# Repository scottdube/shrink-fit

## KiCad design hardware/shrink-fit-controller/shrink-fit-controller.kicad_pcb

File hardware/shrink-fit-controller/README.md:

# Shrink-Fit Induction Controller — PCB

KiCad 10 project. **Milled in-house, single-sided**, so the constraints that
decide this layout are not the ones a board house would impose.

## Scope: full controller, staged populate

Decided 2026-08-25. Every Phase 2 block gets a footprint and a header; only the
Phase 1 blocks get populated now.

The reasoning is *not* the enclosure's "expensive to redo" argument — a milled
board is an afternoon, and copper is the cheap part. It is that **a respin costs
desoldering and re-soldering everything already on the board.** A footprint on a
board you are milling anyway costs nothing, so the asymmetry runs entirely one
way.

Rejected: a Phase-1-minimum board. It would route faster and mill sooner, but it
buys a few hours against a guaranteed rebuild of the one thing on this project
that has to be *reliable* rather than fast.

## Blocks

| | Block | Phase | Parts |
|---|---|---|---|
| ✅ | MCU | 1 | U1 ESP32-S3 Super Mini (HW-747) |
| ✅ | SSR drive | 1 | Q1 2N3904, R1 1 k |
| ✅ | Bus voltage sense | 1 | R2 220 k, R3 10 k, C1 100 nF |
| ✅ | Discrete inputs | 1 | flow switch, E-stop sense, start button |
| ⬜ | Isolated CAN | 2 | U2 SN65HVD230, U3 ADUM1201, U4 B0505S-1W |
| ⬜ | Thermocouple | 2 | U5 MAX31855 (SPI) |
| ⬜ | Bus current / energy | 2 | U6 INA228 (I²C, on the 100 A shunt) |

The SSR-100DD, its heat sink, and the MBR60100PT freewheel diode are
**chassis-mounted, not on this board** — they carry bus current and need the
heat path.

## Pin map — from `firmware/include/config.h`, not restated

| GPIO | Net | Block | Note |
|---|---|---|---|
| 1 | `BUS_SENSE` | bus divider | ADC1_CH0. ADC1 avoids the WiFi conflict on ADC2 |
| 2 | `START_BTN` | input | not GPIO 3 — that's a strapping pin (JTAG source select) |
| 3 | *free* | — | reserved for the Stage-4 encoder |
| 4 | `CAN_TX` | CAN | TWAI. **Idle is recessive = high** — if this sits low before the driver installs, the transceiver jams the bus |
| 5 | `CAN_RX` | CAN | |
| 6 | `FLOW_SW` | interlock | active high = flow proven |
| 7 | `ESTOP_SENSE` | interlock | **read-only status.** The E-stop itself is hardwired in series with the contactor coil (SR-03) and this pin must never be presented as one |
| 8 | `SDA` | I²C | INA228 @ 0x40 |
| 9 | `SCL` | I²C | |
| 10 | `SSR_DRV` | SSR drive | CR-05: this pin delivers the voltage **step**. CAN sets bus voltage and must never enable the output — a ramp is what causes ZVS shoot-through |
| 11 | `TC_CS` | thermocouple | |
| 12 | `TC_SCK` | thermocouple | |
| 13 | `TC_MISO` | thermocouple | |

GPIO 33–37 are electrically free (measured: no PSRAM) but land on inner pads, so
they need soldering rather than a header. Not used.

## Grounding

**The controller floats with the bus, referenced to DC−.** The DC− → earth bond
was withdrawn: the chassis is earthed through the AC cord regardless, and bonding
*creates* a 168 V shock path for the dominant fault (coil → holder).

Consequences that bind this layout:
- The bus divider references DC−, which is board GND. Low-side sensing is
  therefore near zero common mode.
- **CAN must be isolated** — U3/U4 exist for this reason, not for noise.
- **No USB while energised.** The USB shield ties board GND to the host.

## Single-sided layout constraints

- All routing on **B.Cu** with a GND pour on B.Cu. THT parts mount on the bare
  top face and solder on the copper face, so **any SMD part must be flipped to
  B.Cu**.
- Crossings become top-side jumper wires. If it will not route on one layer with
  a pour and a few jumpers, order it instead.
- **Don't thread traces between 0.1" header pads** — ~0.84 mm between 1.7 mm pads
  at 2.54 mm pitch is too tight to isolate reliably. Route around.
- **Socket rows get 1.78 mm pads, not the stock 1.70.** Stock KiCad
  `PinSocket_1x*_P2.54mm_Vertical` passes pcbmill's 0.25 mm annulus gate by
  **9.5 µm** — technically fine, no margin. 1.78 gives 0.300 mm.
- **Zone minimum width ≥ 0.5 mm.** KiCad defaults to 0.25 mm, which lets the pour
  create slivers narrower than the V-bit can cut; the mill leaves them as stray
  copper that looks like nothing on screen.
- Pad connections: **thermal reliefs**, not solid.
- Isolation barrier between CAN primary and secondary gets an explicit **Rule
  Area keepout**, not default clearance.
- **Keepout under the Super Mini's antenna end.**
- **NPTH mechanical holes** (hole, no pad) under any module pin that lands on the
  MCU's internal flash bus, so those pins pass through touching nothing.

## Open — blocking layout

1. ~~Super Mini footprint~~ — **done.** In the project library, verified pad by
   pad. Row spacing **15.24 mm** — see Dimensions.
2. ~~No 5 V / 12 V source~~ — **resolved.** The kit's 12 V 3 A wall wart (#1102)
   plus an LM2596 from stock. 2-prong Class II confirmed, so the earthing
   concern is closed; the pump-noise concern in Power still stands.
3. **Mounting is undecided** because the enclosure is. Holes are free while
   milling and painful to retrofit next to a pour, so the enclosure has to be
   picked — or at least its mounting pattern fixed — before the board outline is.
   **This is now the only thing between here and copper.**

## Super Mini pinout — verified

Read off photographs of both faces of the board (InvenTree part #60, taken
2026-08-15). **HW-747 V0.0.2.** Component side up, USB-C at the top:

| Pin # | Name | | Pin # | Name |
|---|---|---|---|---|
| 1 | TX | | 18 | 5V |
| 2 | RX | | 17 | GND |
| 3 | **GPIO1** | | 16 | 3V3 |
| 4 | GPIO2 | | 15 | GPIO13 |
| 5 | GPIO3 | | 14 | GPIO12 |
| 6 | GPIO4 | | 13 | GPIO11 |
| 7 | GPIO5 | | 12 | **GPIO10** |
| 8 | GPIO6 | | 11 | GPIO9 |
| 9 | GPIO7 | | 10 | GPIO8 |

Left row is pins 1–9 top to bottom; right row is 10–18 bottom to top (DIP order).

> **Wire every net by pin NAME, never by number.** The numbers are header
> positions and the names are GPIOs, so they collide misleadingly — `GPIO1` is
> pin number **3**, and `GPIO10`, which drives the SSR, is pin number **12**.
> Wiring by number lands nets on the wrong GPIO and survives ERC, DRC and visual
> review. After wiring, confirm which pad each net actually landed on in the
> `.kicad_pcb`.

Inner pads (not on the headers, need soldering): 14–17, 19, 21, 33–42, 45–48.
This confirms the `config.h` comment. The **antenna is at the end opposite the
USB-C**; BOOT and RESET buttons are at the USB end.

## Dimensions

From a dimensioned drawing supplied 2026-08-25. It is a **third independent
source** and arrives rotated 90 degrees from both photographs, with the pin
labels still matching — so the pinout above is confirmed by three views in three
orientations, which is the only way to rule out a mirror.

| | mm |
|---|---|
| Board, along the pin rows | **23.50** |
| Board, across the rows | **18.00** |
| Pin 1 to pin 9 centres | **20.32** |

**The 20.32 self-validates the pitch:** 8 gaps x 2.54 = 20.32 exactly. Pitch is
2.54 mm and does not need measuring.

**Derived, not given:** 23.50 - 20.32 = 3.18 mm of board beyond the end pin
centres. If the row is centred, that is **1.59 mm** from each end pin centre to
the board edge — and 1.59 mm is 1/16 inch, which is consistent with symmetry.
Treat it as a prediction to confirm, not a dimension to build on.

### Row spacing — resolved: 15.24 mm (0.600 in)

Settled by a found footprint (see below) whose outline matches the drawing
exactly, and which is self-consistent three ways: holes inset 1.38 mm from the
18.00 edges (matching the photos, where the holes sit well inboard), 0.6 in is
the DIP/breadboard standard, and 15.24 is exactly 6 × 2.54.

**The earlier 17.78 mm prediction here was wrong** — it assumed hole centres near
the pad tips. It was marked "calipers win" for exactly this reason. Optional
zero-cost final check before the first mill: seat the module across a
breadboard's centre channel — it should drop into a 0.6 in straddle.

Still worth a number for the enclosure, though not for the footprint: how far
the **USB-C shell overhangs** the board edge.

## Footprint — done, and the trap it contained

Scott found `ESP32-S3-SuperMini.kicad_mod` online. Geometry: correct in every
checkable dimension (fourth independent source for the pinout). But it was
unusable as-is, and the failure would have been **silent**:

1. **Its pad "numbers" are the silk names** (`TX`, `1`, `5V`…). Our netlist
   addresses pads 1–18 by header position, and the file's pad `"1"` is GPIO1's
   hole — **our pad 3**. Drop it in unchanged and most nets land on the wrong
   pins with no DRC or ERC complaint. Pads were renumbered to header positions
   to match the project symbol.
2. **1.508 mm pads on a 1.0 mm drill fail the mill.** pcbmill snaps 1.0 up to
   the 1.181 bit → 0.164 mm annulus against the 0.25 gate. Now 1.78 mm pads on
   a drill specified as **1.181 exactly** → 0.300 mm.
3. Pad "13" sat at y = −2.5 — an off-grid 0.04 mm typo. Fixed.

Square pad = pin 1 = TX (the source squared 5V). Antenna is at the **+y** end of
the footprint: place a Rule Area keepout there at layout — the reserved band is
noted in the footprint's description.

## Schematic — drawn and verified

Single A3 sheet, local labels, generated by `tools/gen_sch.py` (edit the
generator, not the file, until layout starts). Validation, 2026-08-26:

- **ERC: 0 errors, 0 warnings.**
- **Netlist verified against an expected table**: all 15 U1 nets on the intended
  header-position pads; divider chain (`BUS_V+`→R2→tap→R3/C1, tap→`BUS_SENSE`→
  U1 pad 3) and driver chain (`SSR_DRV`→R1→Q1.B, Q1.C→`SSR_K`, Q1.E→GND)
  confirmed by full membership; TX/RX/GPIO3 no-connects present.
- Cosmetic label overlaps remain near J1/J3 (PWR_FLAG glyphs) — nudge in the GUI
  later; they do not affect connectivity.

Phase 2 blocks are headers only (J7 CAN TTL, J8 MAX31855, J9 INA228 I²C) —
pin order on those headers is ours to define, so nothing was invented; the CAN
isolation stack itself is off-board.

## Power

**Resolved 2026-08-25:** a 12 V supply already exists for the fans and pump.

| Role | Part | Stock |
|---|---|---|
| 12 V -> 5 V logic | [#28 LM2596 Buck ADJ](http://192.168.50.10:8001/web/part/28/) | 15 |
| Isolated fallback | [#491 HLK-5M05B AC-DC 5 V 5 W](http://192.168.50.10:8001/web/part/491/) | 3 |
| CAN-side isolation | [#27 B0505S-1W](http://192.168.50.10:8001/web/part/27/) | 5 |

### The constraint this creates

The controller **must** sit at DC-. That is forced by the sensing, not chosen:
the bus divider references DC- and the INA228 has to touch the shunt. Sensing
dictates the isolation architecture, never the other way round.

An LM2596 is a **non-isolated** buck — output ground is input ground. Feeding the
controller from the 12 V rail therefore ties **12 V PSU V- to 48 V DC-**. If that
supply's negative is earthed, or Y-capped to earth as most SMPS bricks are, then
**DC- is earthed** — which silently re-creates the SR-11 bond that was
deliberately withdrawn, and re-creates it in the one machine where the operator's
hand is inside the coil during the cycle.

**VERIFIED 2026-08-27 from the nameplate.** The supply is a model **1230**, AC 100-240 V in, **12 V 3 A** out, centre-positive, carrying the **Class II double-insulation mark** and a 2-prong plug. Marked *dry location only* — so it belongs on the dry side of the seam, which the layout already puts it on.

**The plug answers the grounding question, and it answers it in the good direction.** Class II means there is no earth conductor, so the
output *cannot* be earth-bonded through its cord and tying V- to DC- imports no
earth reference. The SR-11 concern dissolves for that case.

An earlier draft of this section proposed metering V- against the earth pin of
the supply's own AC cord. **That test does not exist on a 2-prong supply** — there
is no such pin. Corrected test, if one is wanted: meter V- against the
*machine's* chassis earth, which is earthed through the NEMA 6-20 cord. That is
where an unwanted bond would actually appear. Expect open.

**The answer flips if the 12 V supply is not a wall wart.** An enclosed or
open-frame supply (Mean Well LRS and similar) mounted inside the machine has an
earth terminal, is usually Y-capped to it, and frequently bonds V- to earth by
default or by jumper. Confirm which type is fitted before trusting the paragraph
above.

### Residual: the Y-cap, and why it reinforces an existing rule

A switching wall wart typically bridges primary to secondary with a Y-cap. That
couples the output to **mains, not earth** — so the whole LV system can float at
roughly half mains AC relative to earth, current-limited to a few hundred uA.
This is the familiar laptop-brick tingle. It is not the SR-11 hazard: there is no
DC fault path and the current is capped.

It does give **"no USB while energised"** a second, independent reason. The host
is earthed, the controller floats, and the USB shield bonds them. The same
applies to an earthed scope ground clip — which matters, because VR-05 calls for
scoping Vds. Use a differential probe or a mains-isolated scope, never a bare
ground clip on this machine. A linear (transformer) wall wart has no Y-cap and
genuinely floats.

### The concern that survives

With earthing resolved, **noise becomes the dominant issue, not safety.** The
same rail runs the pump. An inductive motor sharing the controller's ground
return puts switching transients on the exact reference the bus divider measures
against, and a wall wart sized for a pump will also sag on pump start — which the
ADC sees as a bus-voltage change that never happened.

**STATUS: resolved 2026-08-26.** The 12 V supply is the kit's own wall wart
(#1102, "US or EU plug" per the listing — 2-prong Class II). No earth conductor,
so no back-door SR-11 bond. The LM2596 stands. The pump-noise and start-up-sag
paragraph below is now the binding constraint.

### Independent of that result

The pump and fans must not share the controller's ground return. The pump is
inductive and its switching transients would ride on the very reference the bus
divider measures against. **Star the controller's feed at the PSU terminals** —
never daisy-chained off the pump — plus bulk and ceramic caps at the module
supply pin.

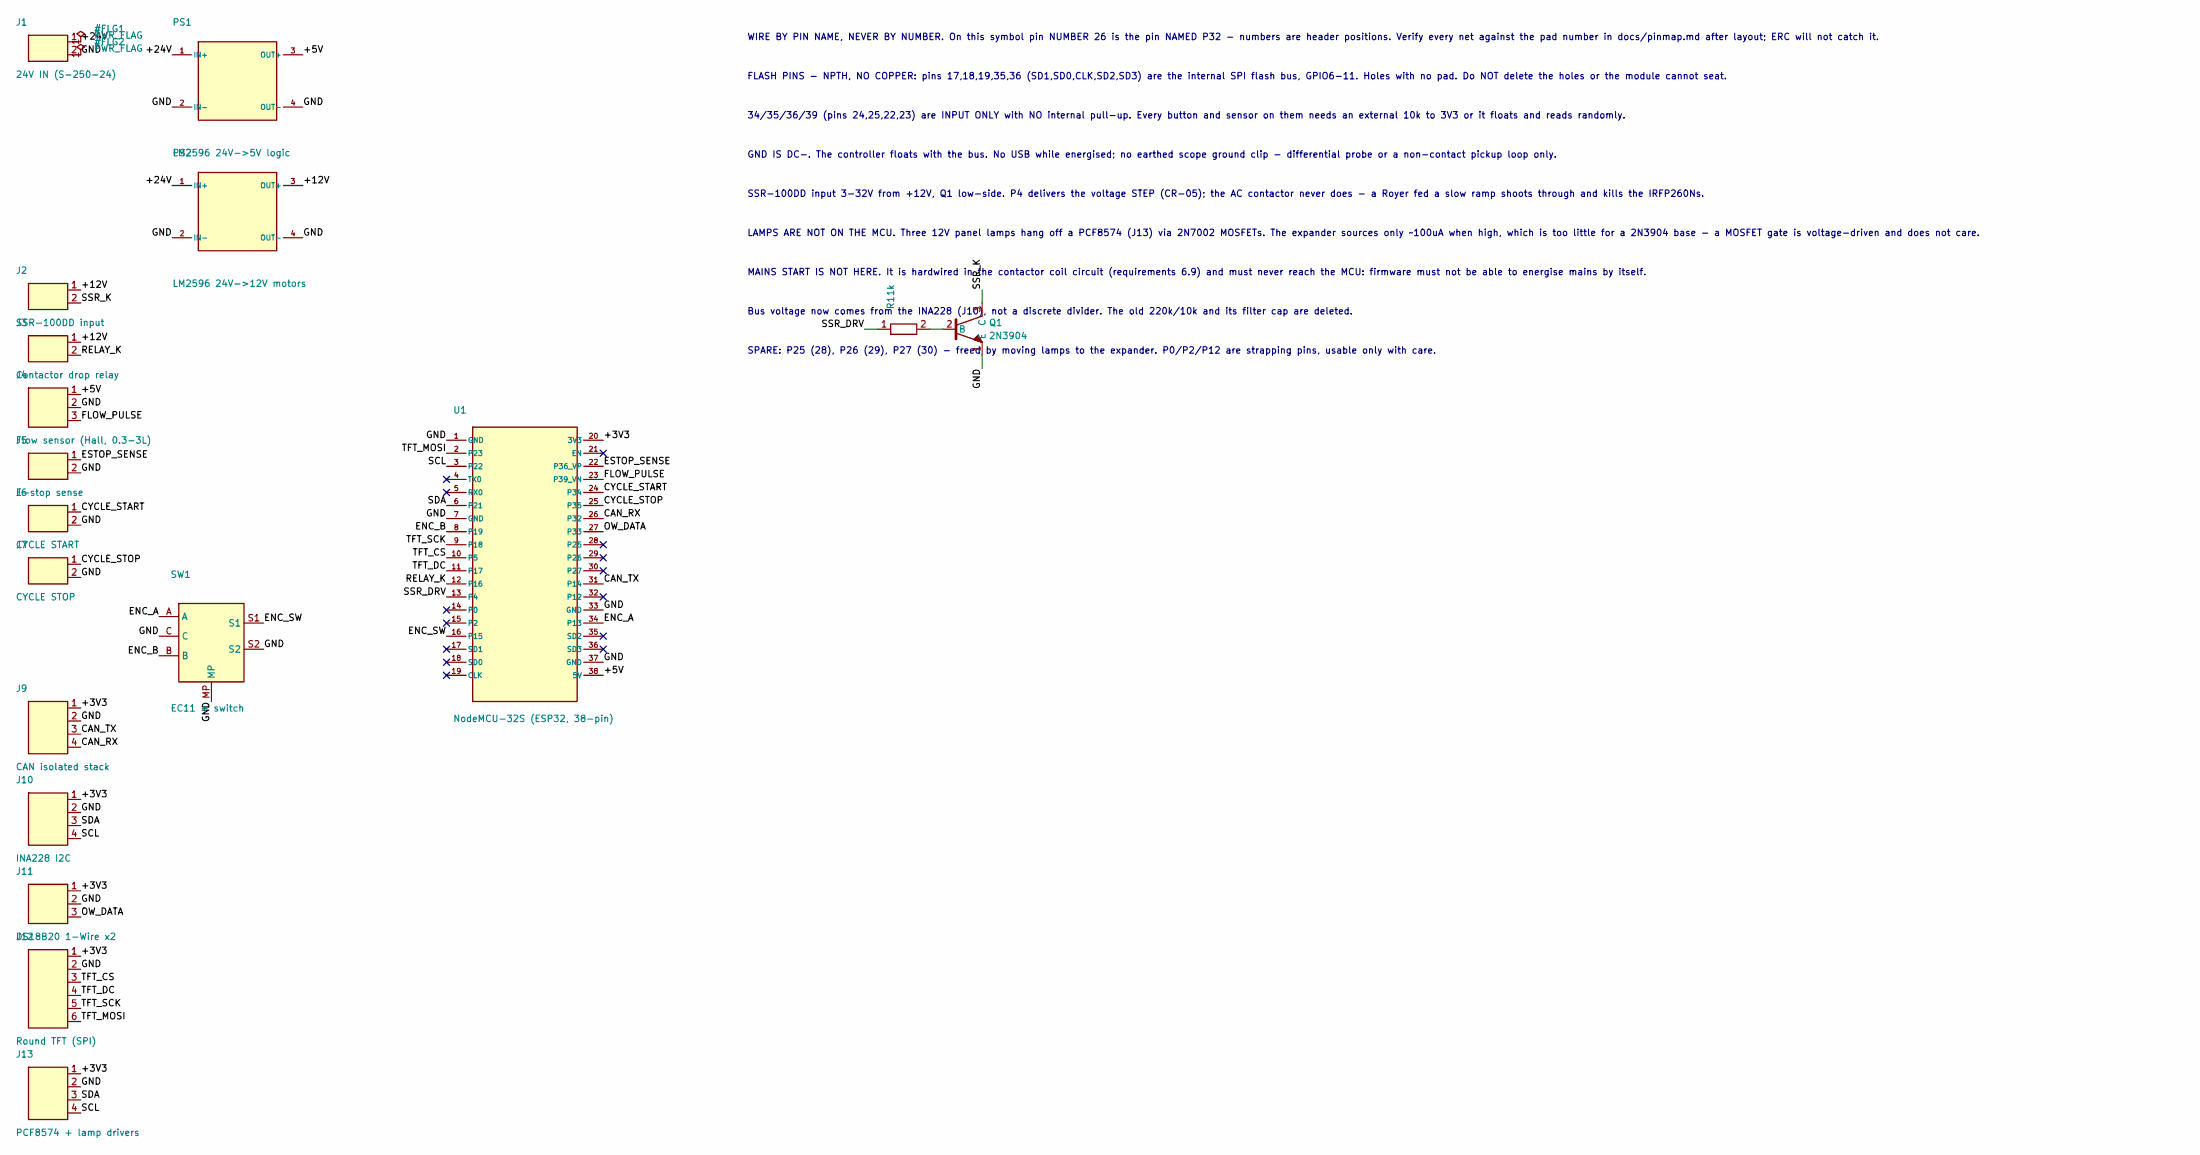
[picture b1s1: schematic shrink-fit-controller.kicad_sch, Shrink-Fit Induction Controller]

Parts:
J1: 24V IN (S-250-24); PinHeader_1x02_P2.54mm_Vertical_1.78pad
J2: SSR-100DD input; PinHeader_1x02_P2.54mm_Vertical_1.78pad
J3: Contactor drop relay; PinHeader_1x02_P2.54mm_Vertical_1.78pad
J4: Flow sensor (Hall, 0.3-3L); PinHeader_1x03_P2.54mm_Vertical_1.78pad
J5: E-stop sense; PinHeader_1x02_P2.54mm_Vertical_1.78pad
J6: CYCLE START; PinHeader_1x02_P2.54mm_Vertical_1.78pad
J7: CYCLE STOP; PinHeader_1x02_P2.54mm_Vertical_1.78pad
J9: CAN isolated stack; PinHeader_1x04_P2.54mm_Vertical_1.78pad
J10: INA228 I2C; PinHeader_1x04_P2.54mm_Vertical_1.78pad
J11: DS18B20 1-Wire x2; PinHeader_1x03_P2.54mm_Vertical_1.78pad
J12: Round TFT (SPI); PinHeader_1x06_P2.54mm_Vertical_1.78pad
J13: PCF8574 + lamp drivers; PinHeader_1x04_P2.54mm_Vertical_1.78pad
PS1: LM2596 24V->5V logic; LM2596_Module_THT
PS2: LM2596 24V->12V motors; LM2596_Module_THT
Q1: 2N3904; TO-92_Inline
R1: 1k; R_Axial_DIN0207_L6.3mm_D2.5mm_P10.16mm_Horizontal
SW1: EC11 + switch; RotaryEncoder_Alps_EC11E-Switch_Vertical_H20mm
U1: NodeMCU-32S (ESP32, 38-pin); NodeMCU-32S_38pin_THT

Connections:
/+3V3: J9.1, J10.1, J11.1, J12.1, J13.1, U1.20 (3V3); also elsewhere on the board
/+5V: J4.1, PS1.3, U1.38 (5V)
/+12V: J2.1, J3.1, PS2.3
/+24V: J1.1, PS1.1, PS2.1
/CAN_RX: J9.4, U1.26 (P32)
/CAN_TX: J9.3, U1.31 (P14)
/CYCLE_START: J6.1, U1.24 (P34)
/CYCLE_STOP: J7.1, U1.25 (P35)
/ENC_A: SW1.A, U1.34 (P13); also elsewhere on the board
/ENC_B: SW1.B, U1.8 (P19); also elsewhere on the board
/ENC_SW: SW1.S1, U1.16 (P15); also elsewhere on the board
/ESTOP_SENSE: J5.1, U1.22 (P36_VP)
/FLOW_PULSE: J4.3, U1.23 (P39_VN)
/GND: J1.2, J4.2, J5.2, J6.2, J7.2, J9.2, J10.2, J11.2, J12.2, J13.2, PS1.2, PS1.4, PS2.2, PS2.4, Q1.1 (E), SW1.C, SW1.MP, SW1.S2, U1.1 (GND), U1.7 (GND), U1.33 (GND), U1.37 (GND); also elsewhere on the board
/OW_DATA: J11.3, U1.27 (P33)
/RELAY_K: J3.2, U1.12 (P16)
/SCL: J10.4, J13.4, U1.3 (P22)
/SDA: J10.3, J13.3, U1.6 (P21)
/SSR_DRV: R1.1, U1.13 (P4)
/SSR_K: J2.2, Q1.3 (C)
/TFT_CS: J12.3, U1.10 (P5)
/TFT_DC: J12.4, U1.11 (P17)
/TFT_MOSI: J12.6, U1.2 (P23)
/TFT_SCK: J12.5, U1.9 (P18)
unnamed: Q1.2 (B), R1.2

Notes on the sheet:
WIRE BY PIN NAME, NEVER BY NUMBER. On this symbol pin NUMBER 26 is the pin NAMED P32 - numbers are header positions. Verify every net against the pad number in docs/pinmap.md after layout; ERC will not catch it.
FLASH PINS - NPTH, NO COPPER: pins 17,18,19,35,36 (SD1,SD0,CLK,SD2,SD3) are the internal SPI flash bus, GPIO6-11. Holes with no pad. Do NOT delete the holes or the module cannot seat.
34/35/36/39 (pins 24,25,22,23) are INPUT ONLY with NO internal pull-up. Every button and sensor on them needs an external 10k to 3V3 or it floats and reads randomly.
GND IS DC-. The controller floats with the bus. No USB while energised; no earthed scope ground clip - differential probe or a non-contact pickup loop only.
SSR-100DD input 3-32V from +12V, Q1 low-side. P4 delivers the voltage STEP (CR-05); the AC contactor never does - a Royer fed a slow ramp shoots through and kills the IRFP260Ns.
LAMPS ARE NOT ON THE MCU. Three 12V panel lamps hang off a PCF8574 (J13) via 2N7002 MOSFETs. The expander sources only ~100uA when high, which is too little for a 2N3904 base - a MOSFET gate is voltage-driven and does not care.
MAINS START IS NOT HERE. It is hardwired in the contactor coil circuit (requirements 6.9) and must never reach the MCU: firmware must not be able to energise mains by itself.
Bus voltage now comes from the INA228 (J10), not a discrete divider. The old 220k/10k and its filter cap are deleted.
SPARE: P25 (28), P26 (29), P27 (30) - freed by moving lamps to the expander. P0/P2/P12 are strapping pins, usable only with care.

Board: 2 copper layers, 18 parts (0 on the bottom side), 25 nets, no tracks yet.

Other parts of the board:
J8: Encoder EC11; PinHeader_1x05_P2.54mm_Vertical_1.78pad

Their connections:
/+3V3: J8.1; also elsewhere on the board
/ENC_A: J8.3; also elsewhere on the board
/ENC_B: J8.4; also elsewhere on the board
/ENC_SW: J8.5; also elsewhere on the board
/GND: J8.2; also elsewhere on the board

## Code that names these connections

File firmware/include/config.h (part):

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// energise it. GPIO 16 can only ever open the contactor.
#define SSR_PIN            4      // via 2N3904, pattern proven on the test rig
#define MAINS_DROP_PIN     16     // controller's path to kill mains; active HIGH = drop
#define ESTOP_SENSE_PIN    36     // input-only; read-only status. The trip is hardwired.

// ---- Operator inputs ----------------------------------------------------------
// BENCH RIG DIVERGES FROM pinmap.md HERE, deliberately (Scott, 2026-09-07).
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// Button straight from pin to GND. Nothing else.
#define START_BUTTON_PIN   27     // CYCLE START, momentary to GND, internal pull-up
#define STOP_BUTTON_PIN    26     // CYCLE STOP — a firmware abort, NOT the E-stop
#define ENC_A_PIN          13     // rotary encoder, PCNT quadrature
#define ENC_B_PIN          19
#define ENC_SW_PIN         15     // strapping pin: must be HIGH at boot. A pulled-up
                                  // button idles HIGH, so this works — by luck. Re-check
                                  // if the switch is ever changed to active-high.

// ---- Sensors ------------------------------------------------------------------
#define FLOW_PULSE_PIN     39     // Hall flow sensor, pulses; PCNT counts them (CR-06)
#define ONEWIRE_PIN        33     // both DS18B20 coolant probes (CR-07)
// NO ON-BOARD THERMOCOUPLE. pinmap.md: "MAX31855 / thermocouple. Deleted — CR-02
// rewritten." A TC in a kW-class 90 kHz field cannot be read during a cycle
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// ---- Buses --------------------------------------------------------------------
#define I2C_SDA_PIN        21     // INA228 (0x40) and the PCF8574 lamp expander
#define I2C_SCL_PIN        22
#define CAN_TX_PIN         GPIO_NUM_14   // TWAI. pinmap: P14 = header pin 31
#define CAN_RX_PIN         GPIO_NUM_32   // TWAI. pinmap: P32 = header pin 26 — NOT GPIO 12,
                                         // whose boot-strap a HIGH-idling RX would break
#define CAN_BITRATE_KBPS   125    // MEASURED on the rectifier 2026-09-07 (§6.14.0a)

// ---- Display and lamps --------------------------------------------------------
#define TFT_CS_PIN         5
#define TFT_DC_PIN         17
#define TFT_SCK_PIN        18     // VSPI default
#define TFT_MOSI_PIN       23     // VSPI default; MISO unused, display is write-only
// Lamps live on the PCF8574 (2N7002 gate drive — the expander cannot source enough
// for a 2N3904). Address is 0x20 for a PCF8574P, 0x38 for a PCF8574AP: READ THE
// CHIP MARKING before trusting this constant (pinmap.md, Bridgold listing
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
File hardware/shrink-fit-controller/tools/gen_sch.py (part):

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SW1X, SW1Y = 66.04, 140.97
instance("RotaryEncoder_EC11","SW1","EC11 + switch",SW1X,SW1Y,0,6,SW1X-8,SW1Y-12,SW1X-8,SW1Y+14,
         fp="Rotary_Encoder:RotaryEncoder_Alps_EC11E-Switch_Vertical_H20mm")
label("ENC_A", SW1X-10.16, SW1Y-3.81, 180)
label("GND",   SW1X-10.16, SW1Y,      180)
label("ENC_B", SW1X-10.16, SW1Y+3.81, 180)
label("ENC_SW",SW1X+10.16, SW1Y-2.54, 0)
label("GND",   SW1X+10.16, SW1Y+2.54, 0)
label("GND",   SW1X,       SW1Y+12.70, 270)
conn("J9", "CAN isolated stack",          4, 154.94, ["+3V3","GND","CAN_TX","CAN_RX"])
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    else:   nc(x, y)

# ---- SSR driver : unchanged, 2N3904 off a real GPIO that can source ----------
label("SSR_DRV",193.04,81.28,180)
wire(193.04,81.28,195.58,81.28)
instance("R","R1","1k",200.66,81.28,90,2,198.12,77.47,198.12,74.93,
         fp="Resistor_THT:R_Axial_DIN0207_L6.3mm_D2.5mm_P10.16mm_Horizontal")
wire(205.74,81.28,208.28,81.28)
instance("Q_2N3904","Q1","2N3904",213.36,81.28,0,3,217.17,80.01,217.17,82.55,
         fp="Package_TO_SOT_THT:TO-92_Inline")
wire(215.9,76.2,215.9,73.66); label("SSR_K",215.9,73.66,90)
wire(215.9,86.36,215.9,88.9); label("GND",215.9,88.9,270)

# ---- notes ----
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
